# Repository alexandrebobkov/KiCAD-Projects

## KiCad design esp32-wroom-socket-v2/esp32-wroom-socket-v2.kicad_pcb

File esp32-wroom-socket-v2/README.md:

# ESP32-WROOM-32D Socket Adapter

<p>To-do:</p>

- [ ] Programming switch
- [ ] Systemt status and Power-on LEDs (https://github.com/alexandrebobkov/KiCAD-Projects/issues/2)

> [!CAUTION]
> Do Not Use pins 17, 18, 19, 20, 21 & 22

<p>Power pins: pin #2 +3V3, pins #15 and 38: GND</p>

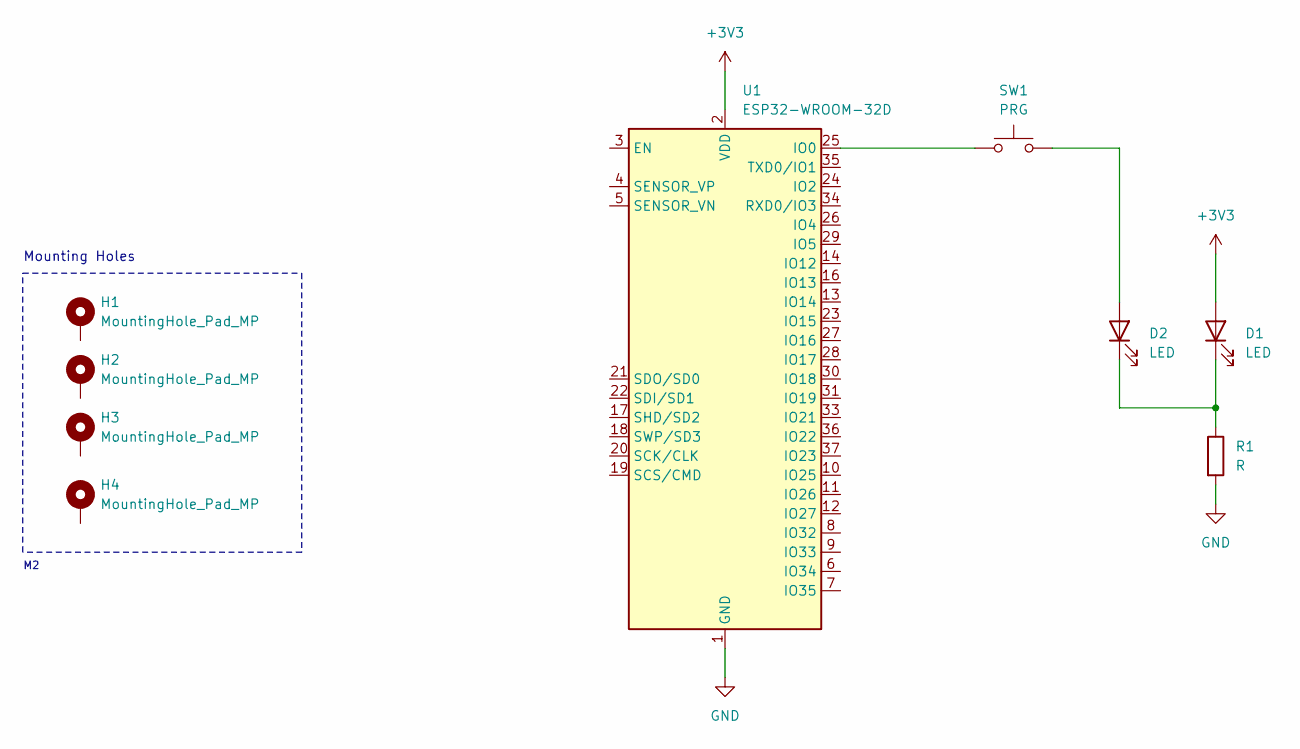
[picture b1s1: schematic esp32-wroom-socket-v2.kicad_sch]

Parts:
D1, D2: LED; LED_2.5mm
H1, H2, H3, H4: MountingHole_Pad_MP; MountingHole_2.2mm_M2
R1: R; R_2.5mm
SW1: PRG; SW_SPST_EVQPE1
U1: ESP32-WROOM-32D; ESP32-WROOM-Adapter-2

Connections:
+3V3: D1.2 (A), U1.2 (VDD)
GND: R1.2, U1.1 (GND), U1.15 (GND), U1.38 (GND), U1.39 (GND)
unnamed: D1.1 (K), D2.1 (K), R1.1
unnamed: D2.2 (A), SW1.2
unnamed: SW1.1, U1.25 (IO0)

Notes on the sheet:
Mounting Holes

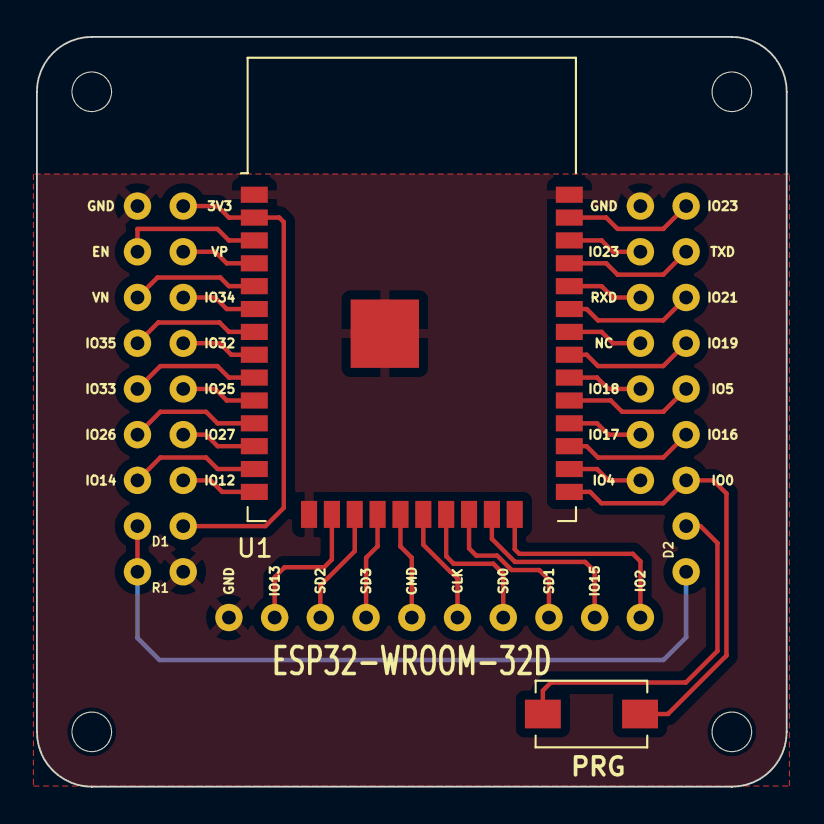
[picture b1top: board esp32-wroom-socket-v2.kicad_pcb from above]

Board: 2 copper layers, 41.7 x 41.7 mm, 9 parts (0 on the bottom side), 5 nets.

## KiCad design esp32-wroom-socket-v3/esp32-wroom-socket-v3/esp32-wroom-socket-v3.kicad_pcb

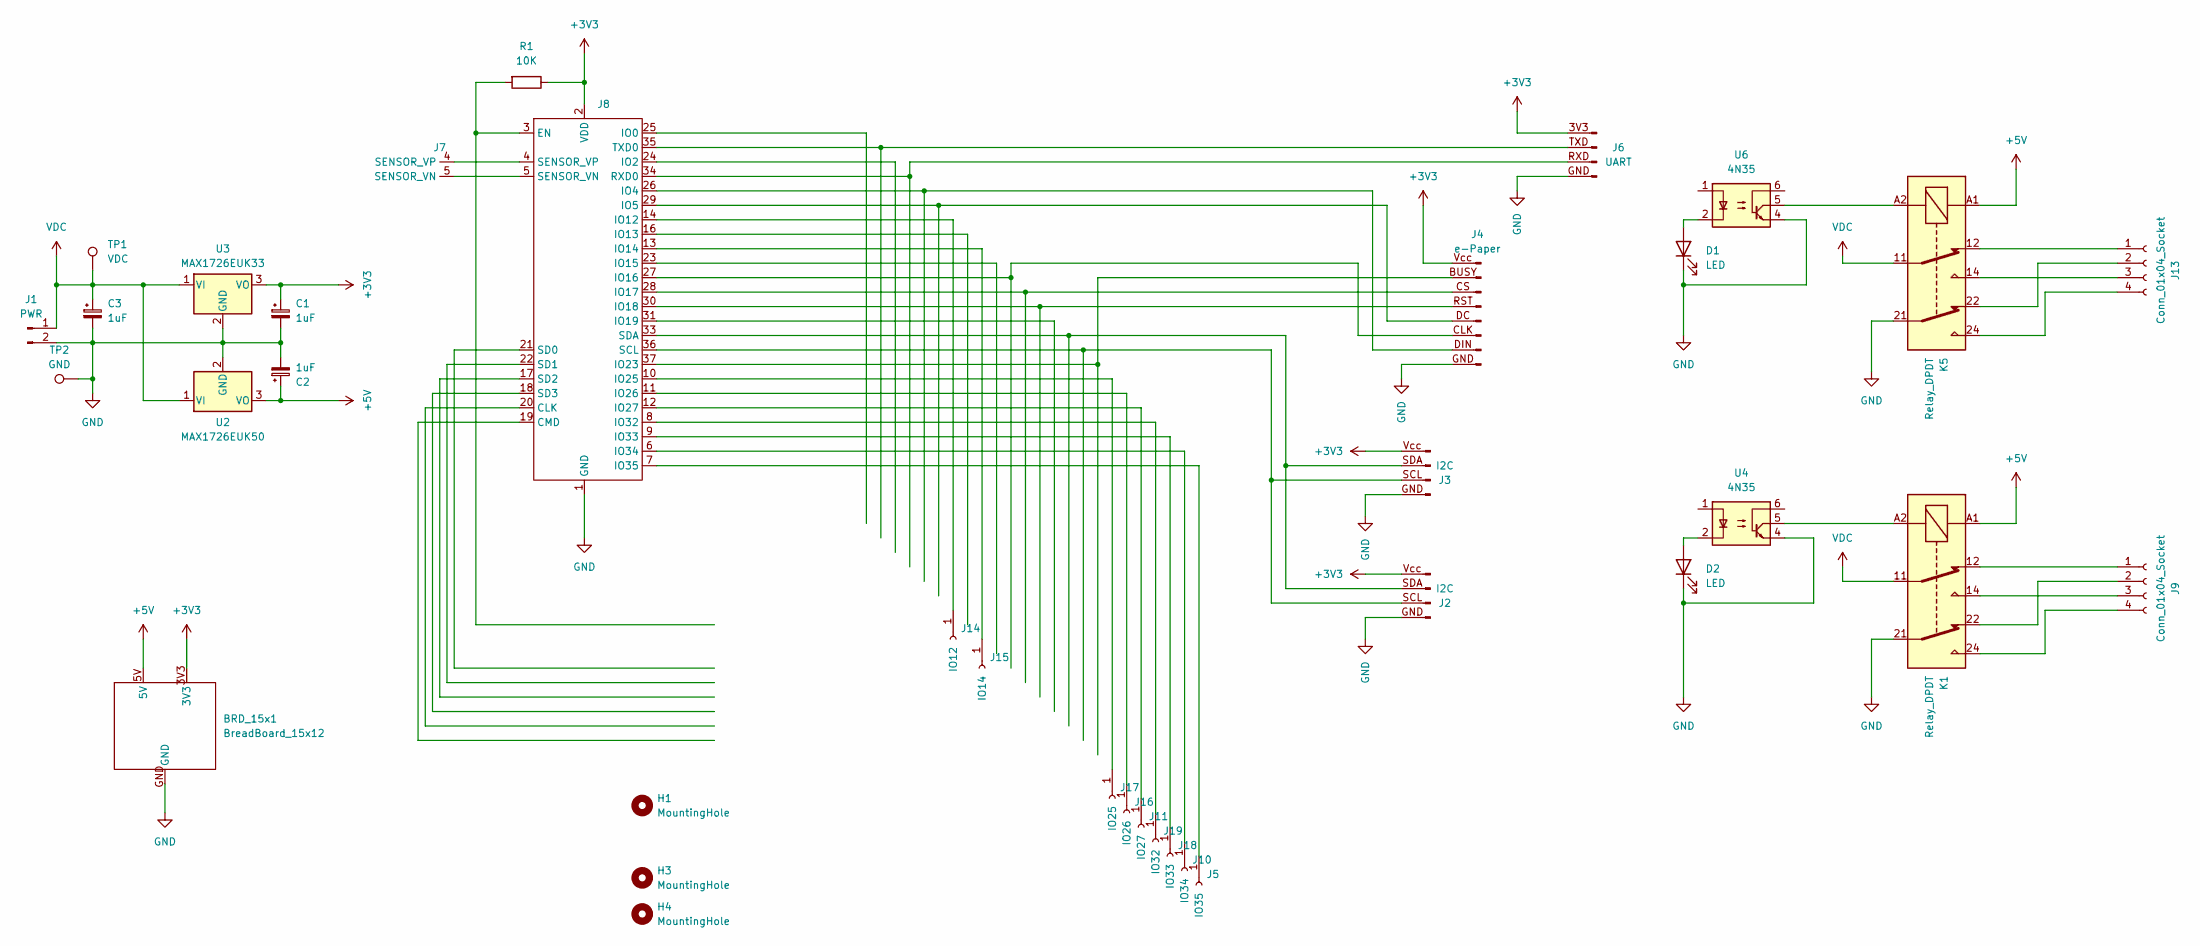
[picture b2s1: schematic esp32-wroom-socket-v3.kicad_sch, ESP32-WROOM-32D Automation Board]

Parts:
BRD_15x1: BreadBoard_15x12
C1, C2, C3: 1uF; CP_Radial_D4.0mm_P2.00mm
D1, D2: LED; LED_2010_5025Metric_Pad1.52x2.65mm_HandSolder
H1, H3, H4: MountingHole; MountingHole_3mm_Pad_TopBottom
J1: PWR; PinHeader_1x02_P2.54mm_Vertical
J2, J3: I2C; Conn_I2C_3
J4: e-Paper; Conn_ePaper
J5: IO35; PinHeader_1x01_P2.54mm_Vertical
J6: UART; Conn_UART
J7: ESP32_PADS_VN-VP
J8: ESP32-WROOM-Adapter-Socket
J9, J13: Conn_01x04_Socket; Conn_Terminal_4_Large
J10: IO34; PinHeader_1x01_P2.54mm_Vertical
J11: IO27; PinHeader_1x01_P2.54mm_Vertical
J14: IO12; PinHeader_1x01_P2.54mm_Vertical
J15: IO14; PinHeader_1x01_P2.54mm_Vertical
J16: IO26; PinHeader_1x01_P2.54mm_Vertical
J17: IO25; PinHeader_1x01_P2.54mm_Vertical
J18: IO33; PinHeader_1x01_P2.54mm_Vertical
J19: IO32; PinHeader_1x01_P2.54mm_Vertical
K1, K5: Relay_DPDT; Relay_DPDT_Finder_30.22
R1: 10K; STA_RMCF1206_STP-L
TP1: VDC; TestPoint_Pad_D1.0mm
TP2: GND; TestPoint_Pad_D1.0mm
U2: MAX1726EUK50; SOT-223-3_TabPin2
U3: MAX1726EUK33; SOT-223-3_TabPin2
U4, U6: 4N35; DIP-6_W7.62mm

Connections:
+3V3: BRD_15x1.3V3, C1.1, J2.Vcc (VCC), J3.Vcc (VCC), J4.Vcc, J6.3V3, J8.2 (VDD), R1.1, U3.3 (VO)
+5V: BRD_15x1.5V, C2.1, K1.A1, K5.A1, U2.3 (VO)
GND: BRD_15x1.GND, C1.2, C2.2, C3.2, D1.1 (K), D2.1 (K), J1.2, J2.GND, J3.GND, J4.GND, J6.GND, J8.1 (GND), K1.21, K5.21, TP2.1, U2.2 (GND), U3.2 (GND), U4.4, U6.4
unnamed: D1.2 (A), U6.2
unnamed: D2.2 (A), U4.2
unnamed: J5.1, J8.7 (IO35)
unnamed: J7.5 (SENSOR_VN), J8.5 (SENSOR_VN)
unnamed: J7.4 (SENSOR_VP), J8.4 (SENSOR_VP)
unnamed: J8.3 (EN), R1.2
unnamed: J4.DIN, J8.26 (IO4)
unnamed: J4.DC, J8.29 (IO5)
unnamed: J4.CLK, J8.27 (IO16)
unnamed: J4.CS, J8.28 (IO17)
unnamed: J4.RST, J8.30 (IO18)
unnamed: J4.BUSY, J8.37 (IO23)
unnamed: J6.RXD, J8.34 (RXD0)
unnamed: J2.SCL, J3.SCL, J8.36 (SCL)
unnamed: J2.SDA, J3.SDA, J8.33 (SDA)
unnamed: J6.TXD, J8.35 (TXD0)
unnamed: J9.1, K1.12
unnamed: J9.2, K1.22
unnamed: J9.3, K1.14
unnamed: J9.4, K1.24
unnamed: J8.6 (IO34), J10.1
unnamed: J8.12 (IO27), J11.1
unnamed: J13.1, K5.12
unnamed: J13.2, K5.22
unnamed: J13.3, K5.14
unnamed: J13.4, K5.24
unnamed: J8.14 (IO12), J14.1
unnamed: J8.13 (IO14), J15.1
unnamed: J8.11 (IO26), J16.1
unnamed: J8.10 (IO25), J17.1
unnamed: J8.9 (IO33), J18.1
unnamed: J8.8 (IO32), J19.1
unnamed: K1.A2, U4.5
unnamed: K5.A2, U6.5
VDC: C3.1, J1.1, K1.11, K5.11, TP1.1, U2.1 (VI), U3.1 (VI)

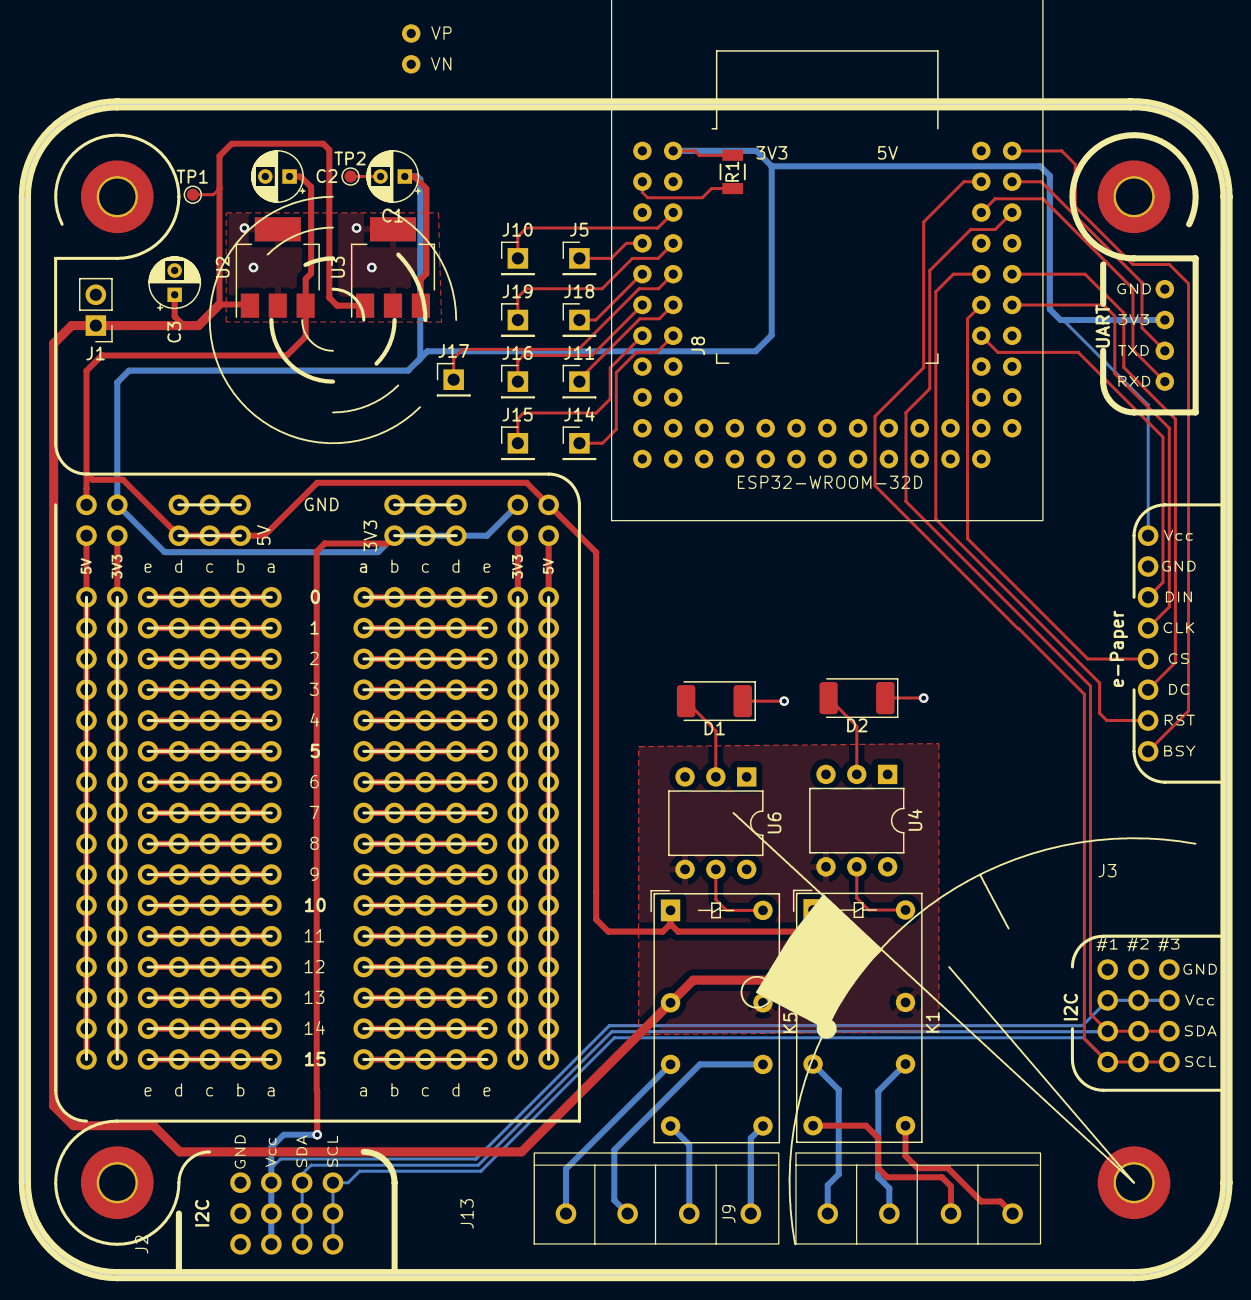
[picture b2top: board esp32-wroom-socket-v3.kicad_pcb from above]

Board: 2 copper layers, 99.1 x 96.5 mm, 37 parts (0 on the bottom side), 38 nets.

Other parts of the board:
H1#2: MountingHole; MountingHole_3mm_Pad_TopBottom

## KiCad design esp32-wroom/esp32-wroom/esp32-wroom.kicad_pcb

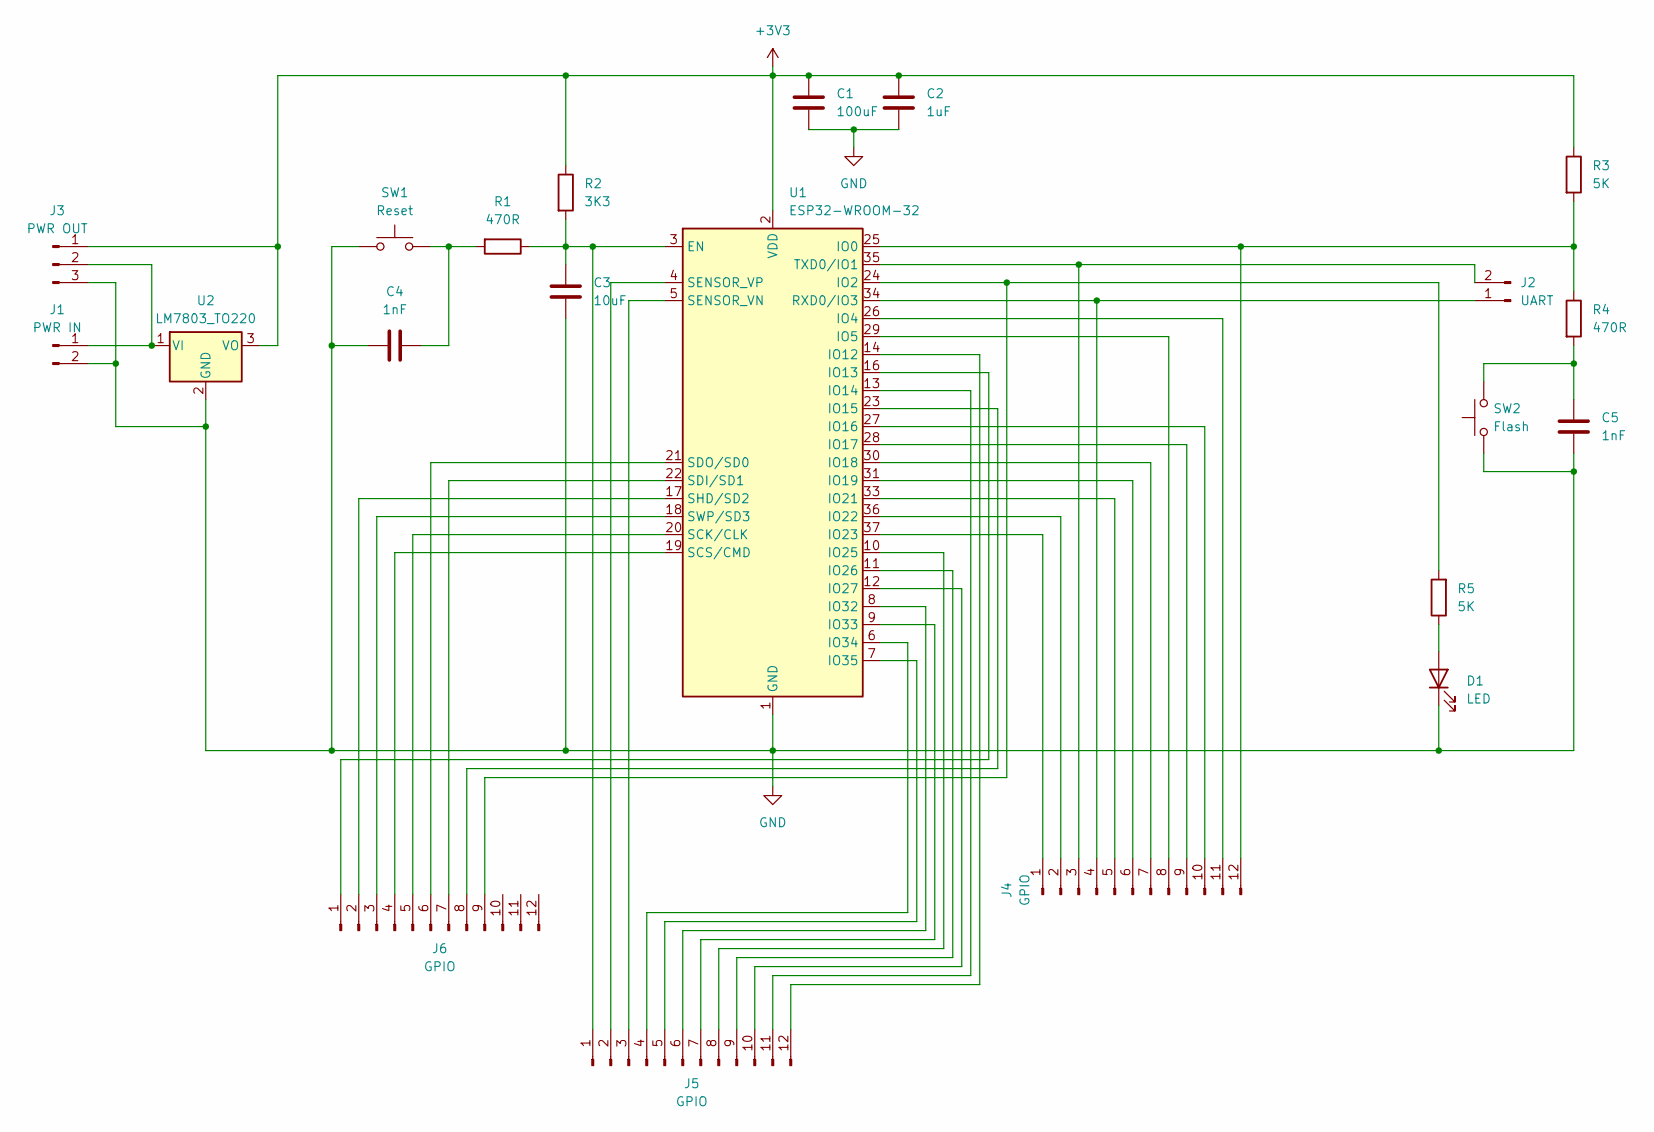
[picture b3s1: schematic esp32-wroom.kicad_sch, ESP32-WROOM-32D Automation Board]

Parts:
C1: 100uF; PinHeader_1x02_P2.54mm_Vertical
C2: 1uF; PinHeader_1x02_P2.54mm_Vertical
C3: 10uF; PinHeader_1x02_P2.54mm_Vertical
C4, C5: 1nF; PinHeader_1x02_P2.54mm_Vertical
D1: LED; PinHeader_1x02_P2.54mm_Vertical
J1: PWR IN; PinHeader_1x02_P2.54mm_Vertical
J2: UART; PinHeader_1x02_P2.54mm_Vertical
J3: PWR OUT; PinHeader_1x03_P2.54mm_Vertical
J4, J5, J6: GPIO; PinHeader_1x12_P2.54mm_Vertical
R1, R4: 470R; R_Axial_DIN0204_L3.6mm_D1.6mm_P2.54mm_Vertical
R2: 3K3; R_Axial_DIN0204_L3.6mm_D1.6mm_P2.54mm_Vertical
R3, R5: 5K; R_Axial_DIN0204_L3.6mm_D1.6mm_P2.54mm_Vertical
SW1: Reset; SW_PUSH_6mm
SW2: Flash; SW_PUSH_6mm
U1: ESP32-WROOM-32; ESP32-WROOM-32D_Alex
U2: LM7803_TO220; TO-220-3_Vertical

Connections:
+3V3: C1.1, C2.1, J3.1, R2.1, R3.1, U1.2 (VDD), U2.3 (VO)
GND: C1.2, C2.2, C3.2, C4.2, C5.2, D1.1 (K), J1.2, J3.3, SW1.1, SW2.1, U1.1 (GND), U1.15 (GND), U1.38 (GND), U1.39 (GND), U2.2 (GND)
unnamed: C4.1, R1.2, SW1.2
unnamed: C5.1, R4.2, SW2.2
unnamed: D1.2 (A), R5.1
unnamed: J1.1, J3.2, U2.1 (VI)
unnamed: J2.1, J4.4, U1.34 (RXD0/IO3)
unnamed: J2.2, J4.3, U1.35 (TXD0/IO1)
unnamed: J4.1, U1.37 (IO23)
unnamed: J4.2, U1.36 (IO22)
unnamed: J4.5, U1.33 (IO21)
unnamed: J4.6, U1.31 (IO19)
unnamed: J4.7, U1.30 (IO18)
unnamed: J4.8, U1.29 (IO5)
unnamed: J4.9, U1.28 (IO17)
unnamed: J4.10, U1.27 (IO16)
unnamed: J4.11, U1.26 (IO4)
unnamed: J4.12, R3.2, R4.1, U1.25 (IO0)
unnamed: C3.1, J5.1, R1.1, R2.2, U1.3 (EN)
unnamed: J5.2, U1.4 (SENSOR_VP)
unnamed: J5.3, U1.5 (SENSOR_VN)
unnamed: J5.4, U1.6 (IO34)
unnamed: J5.5, U1.7 (IO35)
unnamed: J5.6, U1.8 (IO32)
unnamed: J5.7, U1.9 (IO33)
unnamed: J5.8, U1.10 (IO25)
unnamed: J5.9, U1.11 (IO26)
unnamed: J5.10, U1.12 (IO27)
unnamed: J5.11, U1.13 (IO14)
unnamed: J5.12, U1.14 (IO12)
unnamed: J6.1, U1.16 (IO13)
unnamed: J6.2, U1.17 (SHD/SD2)
unnamed: J6.3, U1.18 (SWP/SD3)
unnamed: J6.4, U1.19 (SCS/CMD)
unnamed: J6.5, U1.20 (SCK/CLK)
unnamed: J6.6, U1.21 (SDO/SD0)
unnamed: J6.7, U1.22 (SDI/SD1)
unnamed: J6.8, U1.23 (IO15)
unnamed: J6.9, R5.2, U1.24 (IO2)

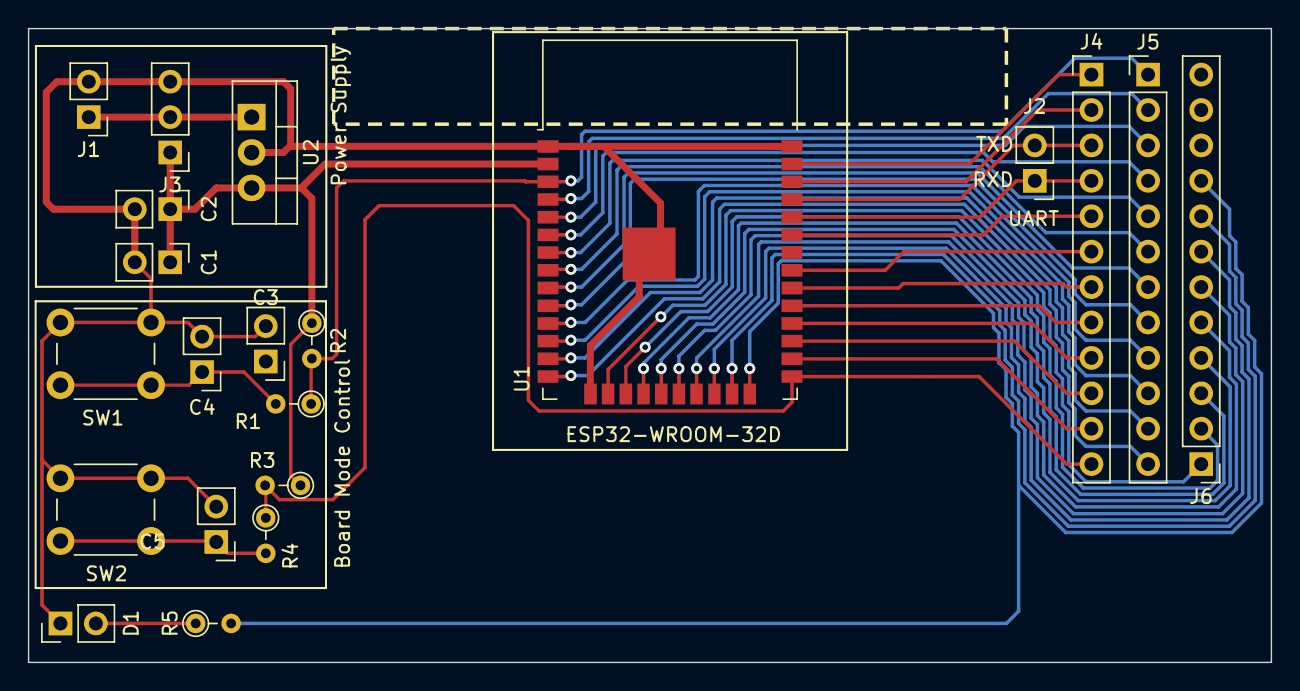
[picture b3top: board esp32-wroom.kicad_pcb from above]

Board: 2 copper layers, 89.2 x 45.5 mm, 21 parts (0 on the bottom side), 39 nets.

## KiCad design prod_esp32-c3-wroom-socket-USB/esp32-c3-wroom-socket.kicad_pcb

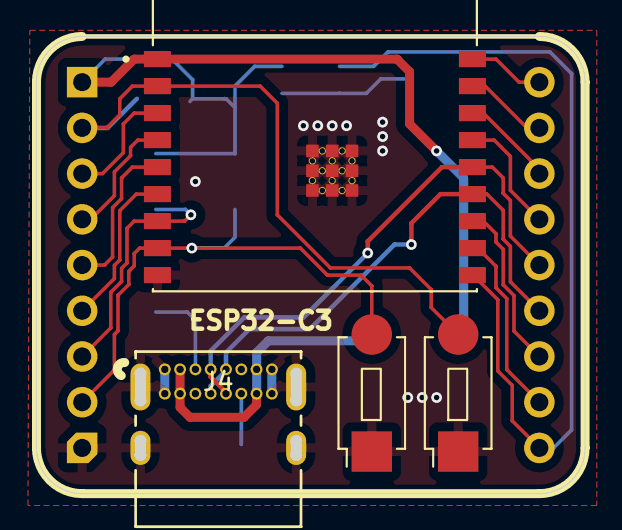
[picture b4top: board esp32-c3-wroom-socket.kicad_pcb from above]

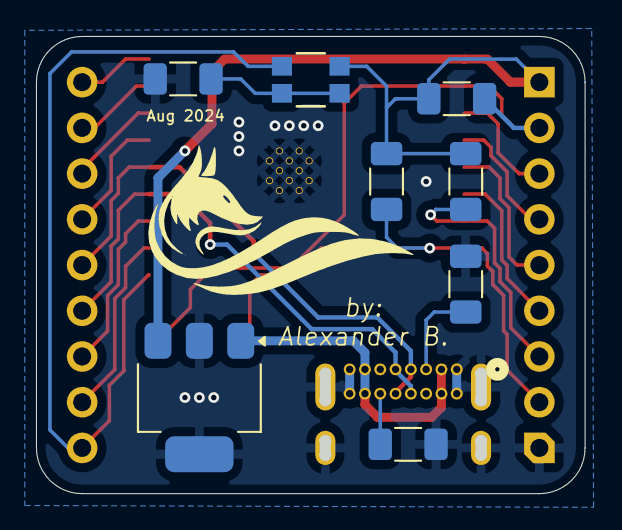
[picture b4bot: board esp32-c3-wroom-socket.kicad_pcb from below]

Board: 2 copper layers, 30.5 x 25.4 mm, 13 parts (8 on the bottom side), 22 nets.

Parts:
J2: Conn_ESP32-C3-WROOM-02
J4: USB-C_Receptacle_Data_16P_GCT-USB4085; USB-C GCT CONN16_USB4085-GF-A
LED1: LED-RED-GREEN-B1552USUG20D; B1552_HVK-M
R1: 10k; R_1206_3216Metric_Pad1.30x1.75mm_HandSolder
R4, R9, R10: 5k1; R_1206_3216Metric_Pad1.30x1.75mm_HandSolder
R7, R8: 2K2; R_1206_3216Metric_Pad1.30x1.75mm_HandSolder
SW1, SW2: SW_Push_SMD_6x3.5; SW_PUSH_6x3.5mm
U1: ESP32-C3-WROOM-02-N4; ESP32-C3-WROOM-02-H4
U2: AMS1117-3V3; SOT-223-3_TabPin2

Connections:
3V3: J2.1, LED1.2 (RED), R1.1, R7.1, R8.1, U1.1 (3V3), U2.3 (VO)
EN: J2.2, R1.2, SW2.2, U1.2 (EN)
GND: J2.9, J4.A1 (GND), J4.A12 (GND), J4.B1 (GND), J4.B12 (GND), J4.S1 (SHIELD), J4.S2 (SHIELD), J4.S3 (SHIELD), J4.S4 (SHIELD), R4.1, R9.1, R10.1, SW1.1, SW2.1, U1.9 (GND), U1.19 (GND__1), U1.20 (GND__2), U1.21 (GND__3), U1.22 (GND__4), U1.23 (GND__5), U1.24 (GND__6), U1.25 (GND__7), U1.26 (GND__8), U1.27 (GND__9), U1.28 (GND__10), U1.29 (GND__11), U1.30 (GND__12), U1.31 (GND__13), U1.32 (GND__14), U1.33 (GND__15), U1.34 (GND__16), U1.35 (GND__17), U1.36 (GND__18), U1.37 (GND__19), U1.38 (GND__20), U1.39 (GND__21), U2.2 (GND)
GPIO0: J2.18, U1.18 (IO0)
GPIO1: J2.17, U1.17 (IO1)
GPIO2: J2.16, U1.16 (IO2)
GPIO3: J2.15, U1.15 (IO3)
GPIO4: J2.3, U1.3 (IO4)
GPIO5: J2.4, U1.4 (IO5)
GPIO6: J2.5, U1.5 (IO6)
GPIO7: J2.6, U1.6 (IO7)
GPIO8: J2.7, R7.2, U1.7 (IO8)
GPIO9: J2.8, R8.2, SW1.2, U1.8 (IO9)
GPIO10: J2.10, LED1.3 (GRN), U1.10 (IO10)
unnamed: J4.A5 (CC1), R10.2
unnamed: J4.B5 (CC2), R9.2
unnamed: LED1.1 (GND), LED1.4 (GND), R4.2
UART-RX: J2.11, U1.11 (RXD)
UART-TX: J2.12, U1.12 (TXD)
USB_D+: J2.14, J4.A6 (D+), J4.B6 (D+), U1.14 (IO19)
USB_D-: J2.13, J4.A7 (D-), J4.B7 (D-), U1.13 (IO18)
VBUS: J4.A4 (VBUS), J4.A9 (VBUS), J4.B4 (VBUS), J4.B9 (VBUS), U2.1 (VI)

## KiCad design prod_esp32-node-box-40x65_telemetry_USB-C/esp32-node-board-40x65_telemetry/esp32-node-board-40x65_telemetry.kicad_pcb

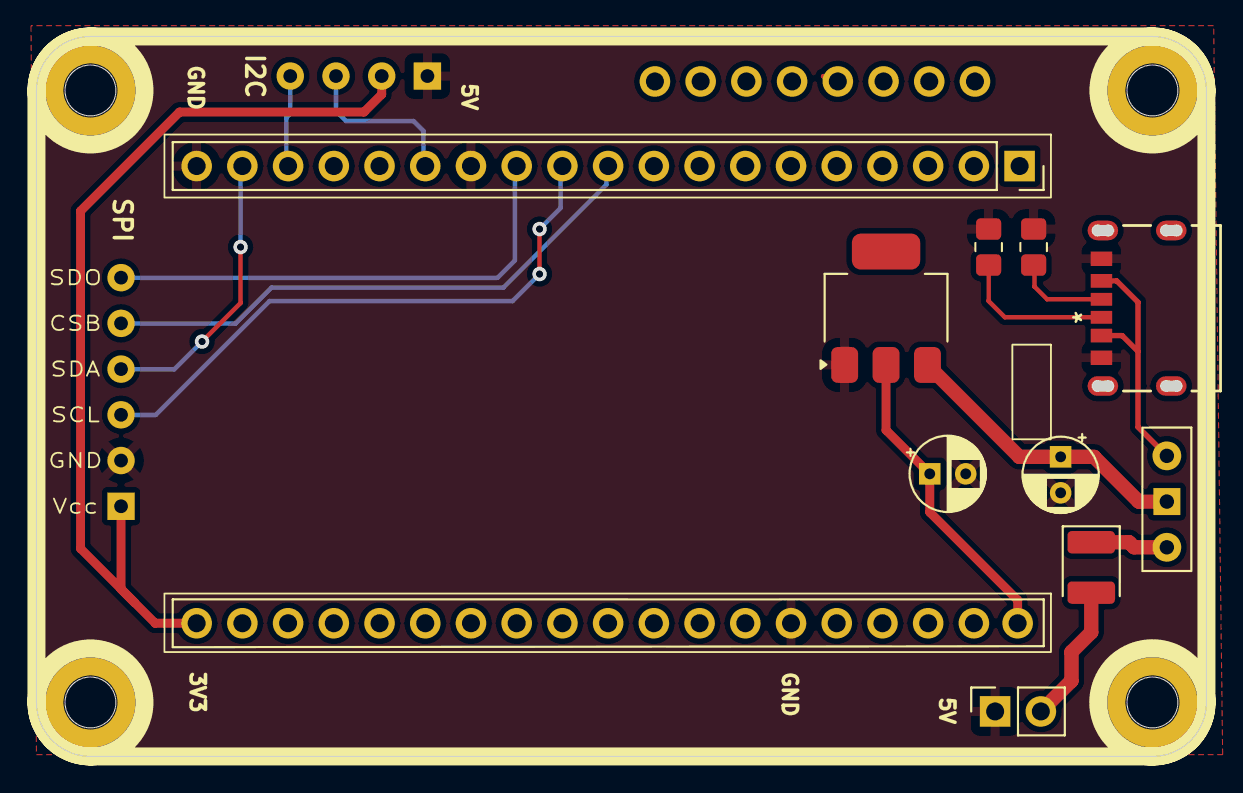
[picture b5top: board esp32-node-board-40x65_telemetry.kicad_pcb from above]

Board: 2 copper layers, 65.0 x 40.0 mm, 14 parts (0 on the bottom side), 15 nets.

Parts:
C1, C2: 1uF; CP_Radial_D4.0mm_P2.00mm
D1: D; D_1210_3225Metric
H1: Project_Box_Board_65x40; Board_65-40
J1: PWR; PinSocket_1x02_P2.54
J3: I2C; Conn_I2C
J5: Conn_SPI
J6: Conn_ESP32_WROOM-DevKit-38pins
J8: USB-C; 2171750001_MOL
J16: e-Paper; Conn_ePaper
R1, R7: 5K1; R_0805_2012Metric_Pad1.20x1.40mm_HandSolder
SW2: SW_SPDT; SW_Slide-03_7.3x2.5x2.5_P2.54mm
U1: AMS1117-5.0; SOT-223-3_TabPin2

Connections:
+3V3: J3.Vcc (VCC), J5.Vcc (VCC), J6.20 (3V3)
+5V: C2.1, J6.38 (5V), U1.2 (VO)
/SCL-2: J3.SCL, J6.17 (22)
/SDA-2: J3.SDA, J6.14 (21)
/SPI-CSB: J5.CSB, J6.10 (5)
/SPI-SCL: J5.SCL, J6.11 (18)
/SPI-SDA: J5.SDA, J6.18 (23)
/SPI-SDO: J5.SDO, J6.12 (19)
/USB-Terminal/VBUS: J8.A9 (VBUS1), J8.B9 (VBUS2)
/VDC: D1.2 (A), J1.2
/VIN: C1.1, SW2.1 (COM), U1.3 (VI)
GND: C1.2, C2.2, H1.1 (GND), H1.2 (GND), H1.3 (GND), H1.4 (GND), J1.1, J3.GND, J5.GND, J6.13 (GND), J6.19 (GND), J6.33 (GND), J8.A12 (GND1), J8.B12 (GND2), R1.2, R7.1, U1.1 (GND)
unnamed: D1.1 (K), SW2.3 (B)
unnamed: J8.A5 (CC1), R1.1
unnamed: J8.B5 (CC2), R7.2

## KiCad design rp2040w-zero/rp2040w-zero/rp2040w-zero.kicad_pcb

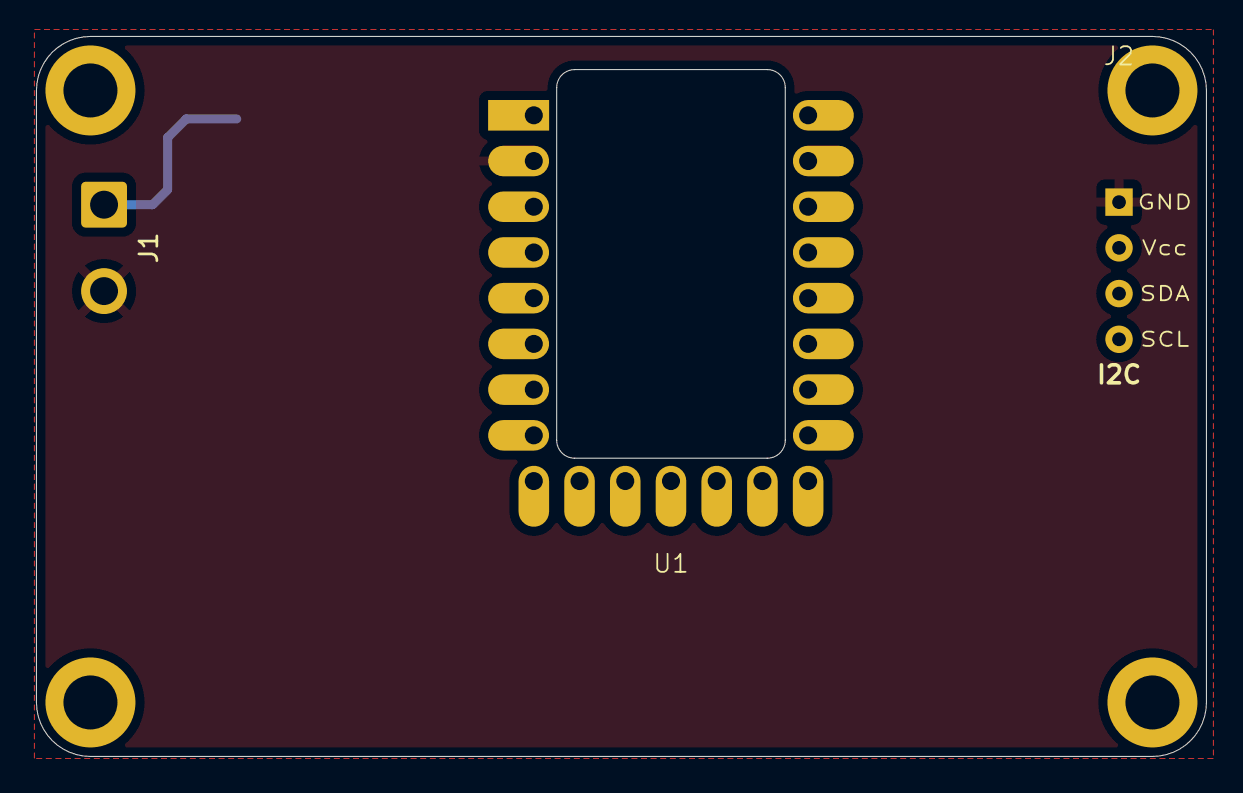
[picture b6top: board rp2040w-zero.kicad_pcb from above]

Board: 2 copper layers, 65.0 x 40.0 mm, 5 parts (1 on the bottom side), 6 nets.

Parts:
BRD1: Board_65-40
J1: PWR; SolderWire-0.75sqmm_1x02_P4.8mm_D1.25mm_OD2.3mm
J2: I2C; Conn_I2C
U1: RP2040-Zero-constellation
U2: LM78M05_TO252; TO-252-2

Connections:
+5V: U1.1 (5V), U2.3 (VO)
/3V3: J2.Vcc (VCC), U1.3 (3V3)
/SCL: J2.SCL, U1.18 (SCL0)
/SDA: J2.SDA, U1.19 (SDA0)
/VCC: J1.1, U2.1 (VI)
GND: J1.2, J2.GND, U1.2 (GND), U2.2 (GND)
